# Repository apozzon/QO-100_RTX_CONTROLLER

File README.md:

# QO-100_RTX_CONTROLLER
QO-100 RTX CONTROLLER
ESP32 CONTROLLER for QO100
 	 	 	 	 	 	 	 	 	 	 	 	 	 	 	 	 
 	QO-100 RTX		IP		SSID		PASSW	 
 	Controller		192.168.0.214		SKYAP2		************	 
 																 
 	ON/OFF		DATV		GPSDO		FAN		…		…		…		…	 

 	V in		V pow		A pow		mW in		W out		W ref		SWR		T air-pow	 
 	13.8		27.5		1.5		10		7,5		0,6		1,788789		19-33	 

DRAFT COPY - SOON IN ENGLISH

Misure
Parametro	Max	PIN	Note
V ingresso	13.8 V	1	Partitore 1:10
V potenza	30V	2	Partitore 1:10
A potenza	10A	3	Parallelo a R 0,1 ohm da 5 W (10A = 1V)
W power in 	5V	4	
W power out	5V	5	
W reflected	5V	6	
C temperatura	60C	11	Apposito modulo digitale

Controlli
Parametro	Stato	PIN	Note
On / Off	0-1	7	Accende e spegne SDR – Arduino sempre on low
DATV	0-1	8	Commuta 12V-18V su Bias-T
Heat	0-1	9	Accende resistenza riscaldamento clima freddo

INSTALLAZIONE IDE E SETTAGGIO BOARD
Setup Steps for Arduino IDE
1.	Open Arduino IDE and go to File > Preferences.
2.	Add Board Manager URL: Paste the following into the "Additional Boards Manager URLs" field:
https://raw.githubusercontent.com/espressif/arduino-esp32/gh-pages/package_esp32_index.json.
3.	Install Boards: Go to Tools > Board > Boards Manager, search for "esp32" and install the latest version by Espressif Systems.
 
NB: se non carica support mettere queste due istruzioni in C:\Users\Andrea.DESKTOP-IK5K4JJ\.arduinoIDE\ arduino-cli.yaml
network:
  connection_timeout: 300s

4.	Select Board: Select Tools > Board > ESP32 Arduino > ESP32S3 Dev Module.
5.	Configure Tools Menu (Crucial for N16R8):
1.	USB CDC On Boot: "Enabled" (Allows Serial.print via USB).
2.	Flash Size: "16MB (128Mb)".
3.	Flash Mode: "QIO 80MHz" or "QOIO 80MHz".
4.	Partition Scheme: "16M Flash (3M APP/9.9M FATFS)" or similar large partition.
5.	PSRAM: "OPI PSRAM".
6.	Upload: Connect the board, select the correct Port, and upload a test sketch. 

ARDUINO
Additional board manager URL: https://espressif.github.io/arduino-esp32/package_esp32_index.json
Board scelta : ESP32S3 Dev Module

Librerie
https://github.com/ESP32Async/AsyncTCP
https://github.com/ESP32Async/ESPAsyncWebServer
DHT kxn

Java aggiunta libreria Google json
tasto destro su Progetto – Build Path -Add External Archives) – Scegliere file scaricato (es.  gson-2.3.1.jar)

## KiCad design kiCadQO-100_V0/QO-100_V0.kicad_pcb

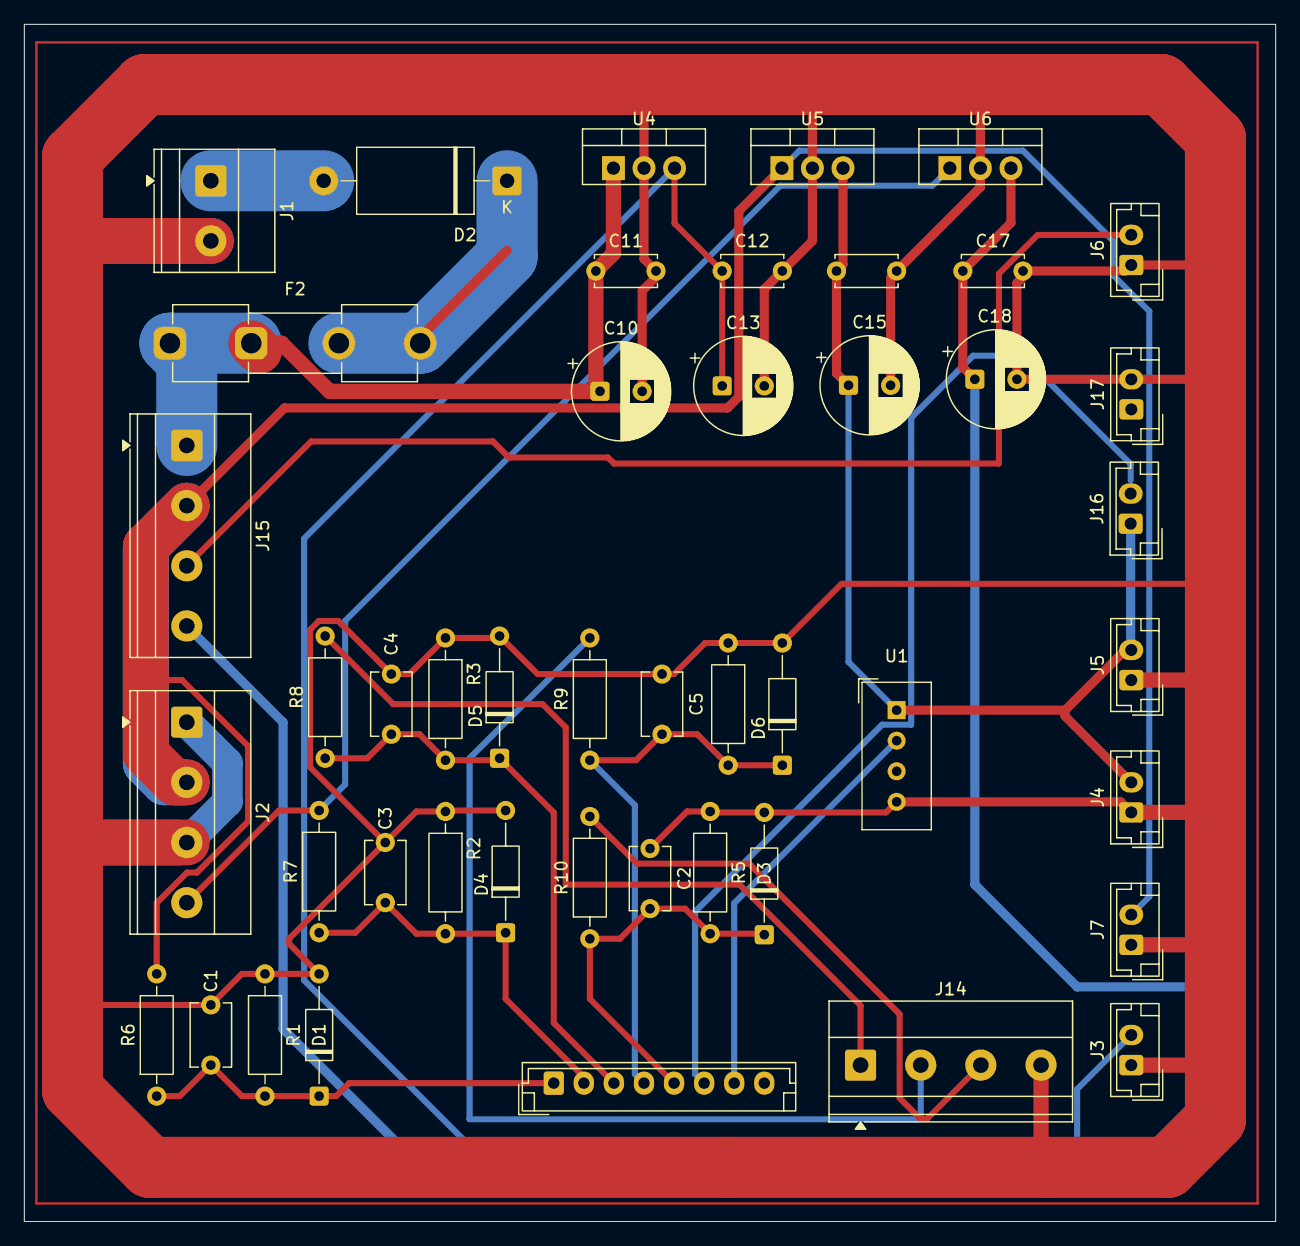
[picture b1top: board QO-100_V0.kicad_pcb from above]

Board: 2 copper layers, 104.0 x 99.5 mm, 46 parts (0 on the bottom side), 20 nets.

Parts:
C1, C2, C3, C4, C5: 100n; C_Disc_D5.1mm_W3.2mm_P5.00mm
C10, C13, C15, C18: 100uF; CP_Radial_D8.0mm_P3.50mm
C11: 330uF; C_Disc_D5.0mm_W2.5mm_P5.00mm
C12, C14, C17: 100nF; C_Disc_D5.0mm_W2.5mm_P5.00mm
D1, D3, D4, D5, D6: 3.3V; D_DO-35_SOD27_P10.16mm_Horizontal
D2: D_Zener 50V-20A; D_DO-27_P15.24mm_Horizontal
F2: Fuse; Fuseholder_Clip-5x20mm_Eaton_1A5601-01_Inline_P20.80x6.76mm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
J1: Conn_01x02; TerminalBlock_Phoenix_MKDS-1,5-2_1x02_P5.00mm_Horizontal
J2: TO DC/DC; TerminalBlock_Phoenix_MKDS-1,5-4_1x04_P5.00mm_Horizontal
J3: ESP32; JST_EH_B2B-EH-A_1x02_P2.50mm_Vertical
J4: Pluto; JST_EH_B2B-EH-A_1x02_P2.50mm_Vertical
J5: GPSDO; JST_EH_B2B-EH-A_1x02_P2.50mm_Vertical
J6: Bias-T; JST_EH_B2B-EH-A_1x02_P2.50mm_Vertical
J7: Preamp; JST_EH_B2B-EH-A_1x02_P2.50mm_Vertical
J13: TO ESP32 Measures; JST_EH_B8B-EH-A_1x08_P2.50mm_Vertical
J14: TO PA - measures; TerminalBlock_Phoenix_MKDS-1,5-4_1x04_P5.00mm_Horizontal
J15: TO RELAIS; TerminalBlock_Phoenix_MKDS-1,5-4_1x04_P5.00mm_Horizontal
J16: TO DHT PA temp; JST_EH_B2B-EH-A_1x02_P2.50mm_Vertical
J17: 5V data n GND; JST_EH_B2B-EH-A_1x02_P2.50mm_Vertical
R1, R3, R4, R5: 20k; R_Axial_DIN0207_L6.3mm_D2.5mm_P10.16mm_Horizontal
R2: 10k; R_Axial_DIN0207_L6.3mm_D2.5mm_P10.16mm_Horizontal
R6, R7, R8, R9, R10: 120k; R_Axial_DIN0207_L6.3mm_D2.5mm_P10.16mm_Horizontal
U1: DHT22 air; Aosong_DHT11_5.5x12.0_P2.54mm
U4, U5: L7805; TO-220-3_Vertical
U6: L7818; TO-220-3_Vertical

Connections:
/IO10: J13.7, U1.2 (DATA)
/IO11: J13.6, J16.2
/Power Supply and partitors/5V Pluto: C14.1, C15.1, J4.2, J5.2, J16.1, U1.1 (VDD), U5.3 (OUT)
/Power Supply and partitors/5V R: C12.1, C13.1, J3.2, U4.3 (OUT)
/Power Supply and partitors/12V: J2.2, J7.2, J15.2, R6.2, U5.1 (IN)
/Power Supply and partitors/12V in R: C10.1, C11.1, F2.1, J15.1, U4.1 (IN)
/Power Supply and partitors/18V R: C17.1, C18.1, J15.4, U6.3 (OUT)
/Power Supply and partitors/28V: J2.4, R7.2, U6.1 (IN)
/Power Supply and partitors/BIAS-T: J6.2, J15.3
GND: C1.1, C2.1, C3.1, C4.1, C5.1, C10.2, C11.2, C12.2, C13.2, C14.2, C15.2, C17.2, C18.2, D1.2 (A), D3.2 (A), D4.2 (A), D5.2 (A), D6.2 (A), J1.2, J2.1, J2.3, J3.1, J4.1, J5.1, J6.1, J7.1, J14.4, J17.2, R1.1, R2.1, R3.1, R4.1, R5.1, U1.4 (GND), U4.2 (GND), U5.2 (GND), U6.2 (GND)
unnamed: C1.2, D1.1 (K), J13.1, R1.2, R6.1
unnamed: D2.2 (A), J1.1
unnamed: D2.1 (K), F2.2
unnamed: C2.2, D3.1 (K), J13.5, R5.2, R10.1
unnamed: C3.2, D4.1 (K), J13.2, R2.2, R7.1
unnamed: C4.2, D5.1 (K), J13.3, R3.2, R8.1
unnamed: C5.2, D6.1 (K), J13.4, R4.2, R9.1
PA W in: J14.1, R8.2
PA W out: J14.2, R9.2
PA W ref: J14.3, R10.2

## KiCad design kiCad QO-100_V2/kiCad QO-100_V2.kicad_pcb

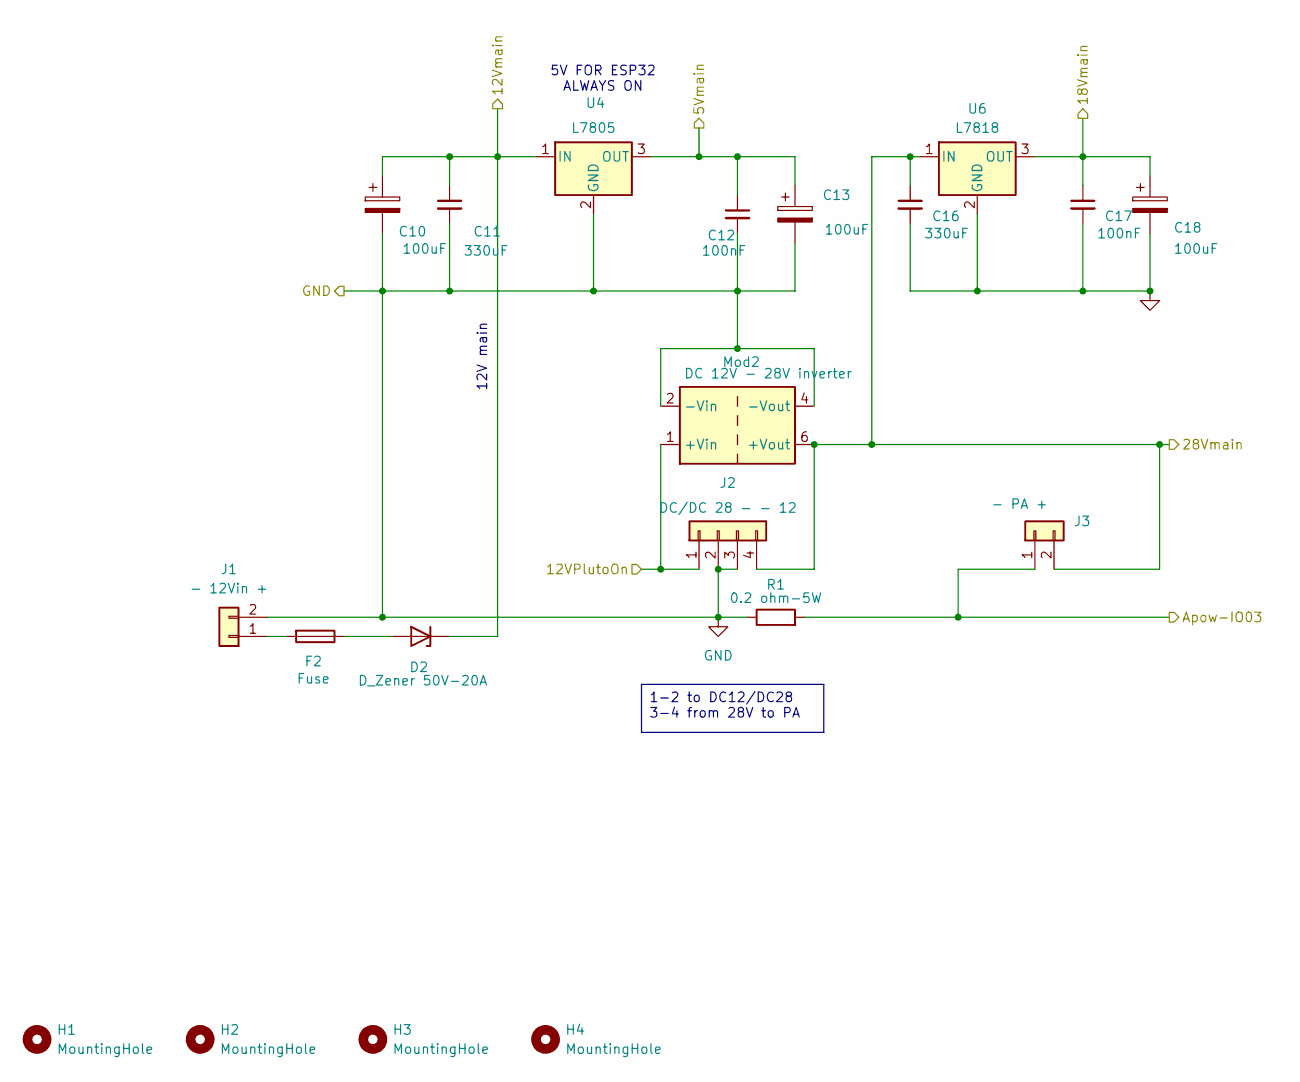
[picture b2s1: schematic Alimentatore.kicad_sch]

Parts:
C10, C13, C18: 100uF; CP_Radial_D8.0mm_P3.50mm
C11, C16: 330uF; C_Disc_D5.0mm_W2.5mm_P5.00mm
C12, C17: 100nF; C_Disc_D5.0mm_W2.5mm_P5.00mm
D2: D_Zener 50V-20A; D_DO-27_P15.24mm_Horizontal
F2: Fuse; Fuseholder_Clip-5x20mm_Eaton_1A5601-01_Inline_P20.80x6.76mm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
H1, H2, H3, H4: MountingHole; MountingHole_3.2mm_M3
J1: - 12Vin +; TerminalBlock_Phoenix_MKDS-1,5-2_1x02_P5.00mm_Horizontal
J2: DC/DC 28 - - 12; TerminalBlock_Phoenix_MKDS-1,5-4_1x04_P5.00mm_Horizontal
J3: - PA +; TerminalBlock_Phoenix_MKDS-1,5-2_1x02_P5.00mm_Horizontal
Mod2: DC 12V - 28V inverter; Converter_DCDC_TRACO_TRA3-xxxx_THT
R1: 0.2 ohm-5W; R_Axial_Power_L20.0mm_W6.4mm_P25.40mm
U4: L7805; TO-220-3_Vertical
U6: L7818; TO-220-3_Vertical

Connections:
/ESP32-S3-DevBoard/5Vmain: C12.1, C13.1, U4.3 (OUT); also elsewhere on the board
/ESP32-S3-DevBoard/12VPlutoOn: J2.1, Mod2.1 (+Vin); also elsewhere on the board
/ESP32-S3-DevBoard/12Vmain: C10.1, C11.1, D2.1 (K), U4.1 (IN); also elsewhere on the board
/ESP32-S3-DevBoard/18Vmain: C17.1, C18.1, U6.3 (OUT); also elsewhere on the board
/ESP32-S3-DevBoard/28Vmain: C16.1, J2.4, J3.2, Mod2.6 (+Vout), U6.1 (IN); also elsewhere on the board
/ESP32-S3-DevBoard/Apow-IO03: J3.1, R1.2; also elsewhere on the board
GND: C10.2, C11.2, C12.2, C13.2, C16.2, C17.2, C18.2, J1.2, J2.2, J2.3, Mod2.2 (-Vin), Mod2.4 (-Vout), R1.1, U4.2 (GND), U6.2 (GND); also elsewhere on the board
unnamed: D2.2 (A), F2.1
unnamed: F2.2, J1.1

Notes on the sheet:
5V FOR ESP32 ALWAYS ON
12V main
1-2 to DC12/DC28 3-4 from 28V to PA

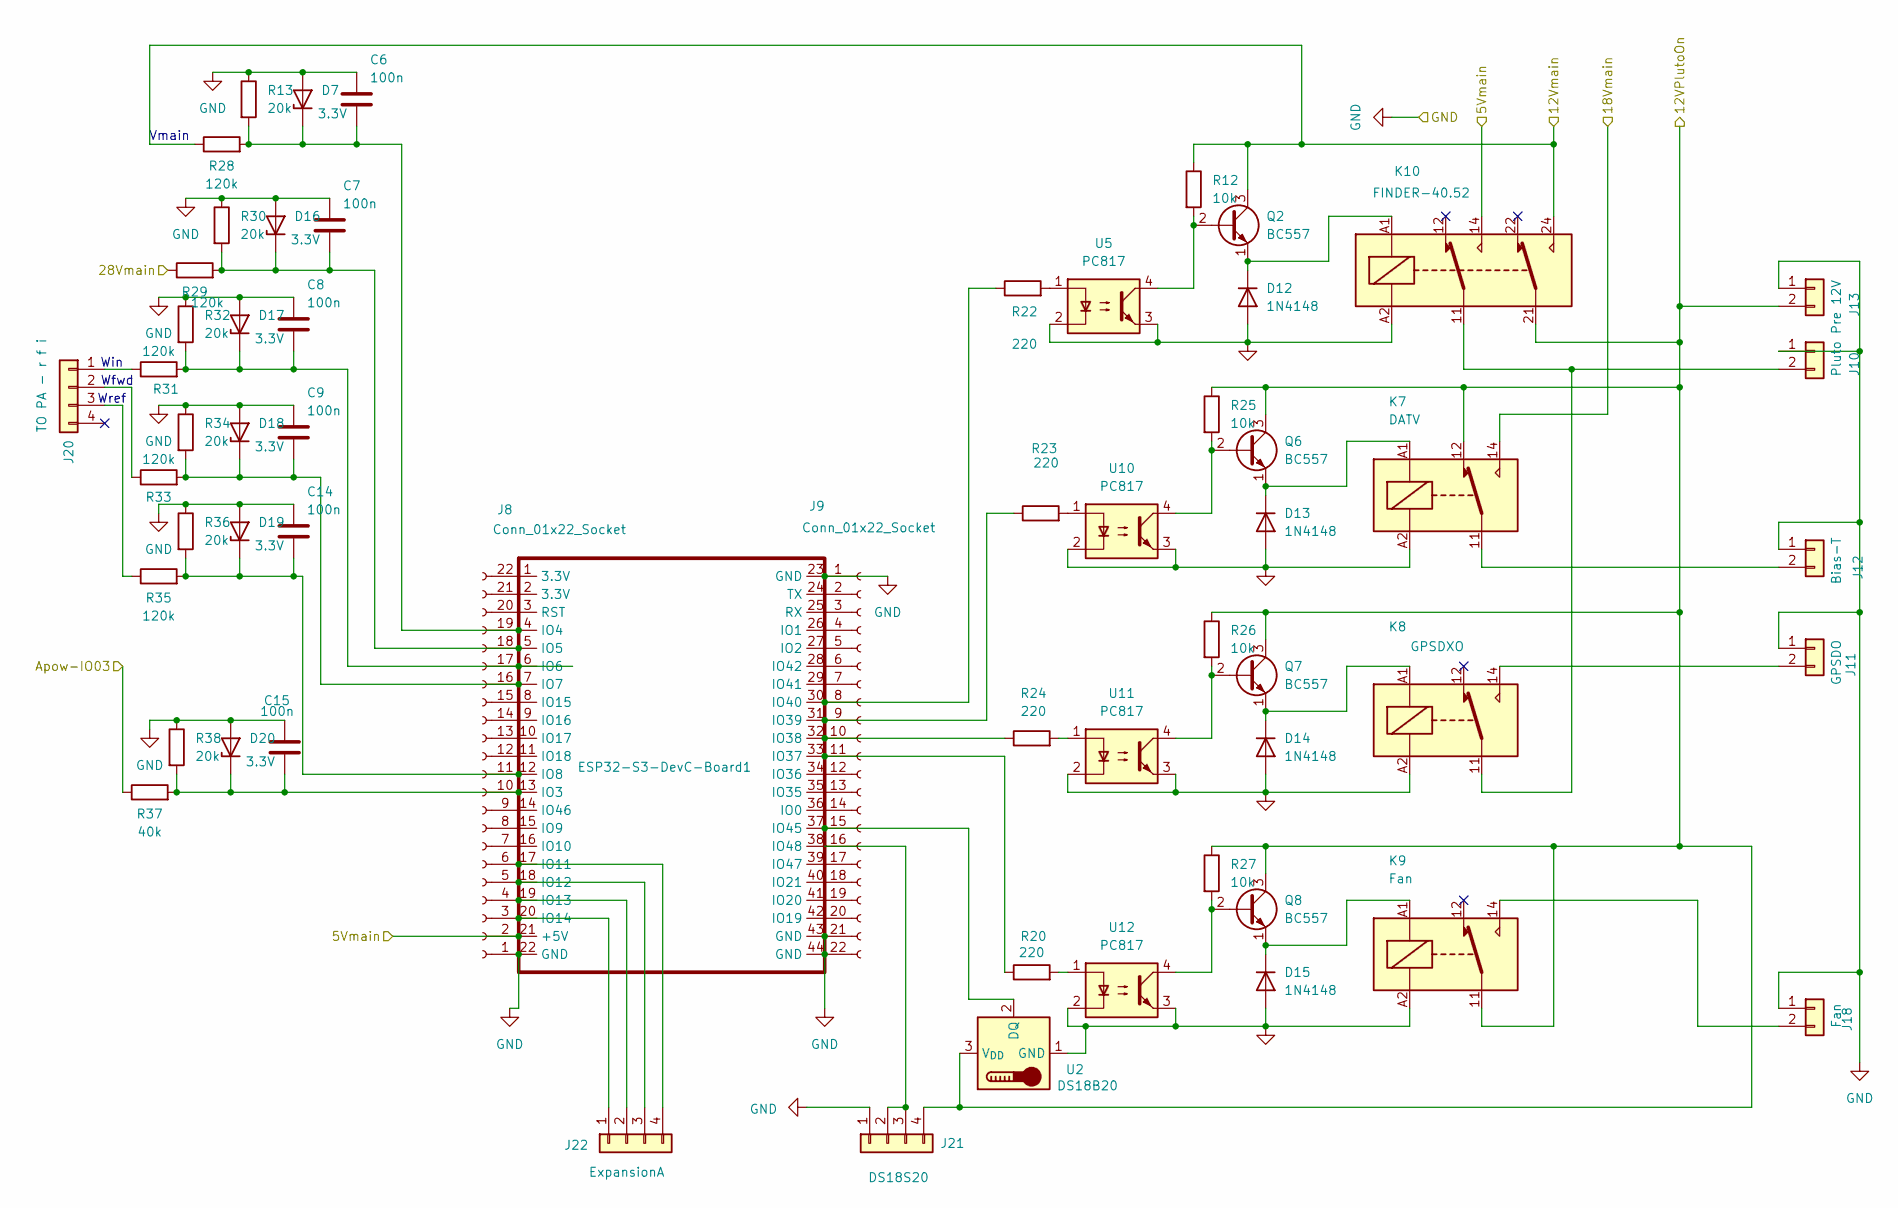
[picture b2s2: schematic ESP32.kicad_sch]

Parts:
C6, C7, C8, C9, C14, C15: 100n; C_Disc_D5.1mm_W3.2mm_P5.00mm
D7, D16, D17, D18, D19, D20: 3.3V; D_DO-35_SOD27_P10.16mm_Horizontal
D12, D13, D14, D15: 1N4148; D_DO-35_SOD27_P7.62mm_Horizontal
ESP32-S3-DevC-Board1: (no value)
J8, J9: Conn_01x22_Socket; PinSocket_1x22_P2.54mm_Vertical
J10: Pluto; JST_EH_B2B-EH-A_1x02_P2.50mm_Vertical
J11: GPSDO; JST_EH_B2B-EH-A_1x02_P2.50mm_Vertical
J12: Bias-T; JST_EH_B2B-EH-A_1x02_P2.50mm_Vertical
J13: Pre 12V; JST_EH_B2B-EH-A_1x02_P2.50mm_Vertical
J18: Fan; JST_EH_B2B-EH-A_1x02_P2.50mm_Vertical
J20: TO PA - r f i; TerminalBlock_Phoenix_MKDS-1,5-4_1x04_P5.00mm_Horizontal
J21: DS18S20; TerminalBlock_Phoenix_MKDS-1,5-4_1x04_P5.00mm_Horizontal
J22: ExpansionA; TerminalBlock_Phoenix_MKDS-1,5-4_1x04_P5.00mm_Horizontal
K7: DATV; Relay_SPDT_Finder_32.21-x000
K8: GPSDXO; Relay_SPDT_Finder_32.21-x000
K9: Fan; Relay_SPDT_Finder_32.21-x000
K10: FINDER-40.52; Relay_DPDT_Finder_40.52
Q2, Q6, Q7, Q8: BC557; TO-92_HandSolder
R12, R25, R26, R27: 10k; R_Axial_DIN0207_L6.3mm_D2.5mm_P10.16mm_Horizontal
R13, R30, R32, R34, R36, R38: 20k; R_Axial_DIN0207_L6.3mm_D2.5mm_P10.16mm_Horizontal
R20, R22, R23, R24: 220; R_Axial_DIN0207_L6.3mm_D2.5mm_P10.16mm_Horizontal
R28, R29, R31, R33, R35: 120k; R_Axial_DIN0207_L6.3mm_D2.5mm_P10.16mm_Horizontal
R37: 40k; R_Axial_DIN0207_L6.3mm_D2.5mm_P10.16mm_Horizontal
U2: DS18B20; TO-92_Inline
U5, U10, U11, U12: PC817; DIP-4_W7.62mm

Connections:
/ESP32-S3-DevBoard/5Vmain: ESP32-S3-DevC-Board1.21 (+5V), J8.2, K10.14; also elsewhere on the board
/ESP32-S3-DevBoard/12VPlutoOn: J13.2, J21.4, K7.12, K9.11, K10.21, Q6.3 (C), Q7.3 (C), Q8.3 (C), R25.1, R26.1, R27.1, U2.3 (V_{DD}); also elsewhere on the board
/ESP32-S3-DevBoard/12Vmain: K10.24, Q2.3 (C), R12.1, R28.1; also elsewhere on the board
/ESP32-S3-DevBoard/18Vmain: K7.14; also elsewhere on the board
/ESP32-S3-DevBoard/28Vmain: R29.1; also elsewhere on the board
/ESP32-S3-DevBoard/Apow-IO03: R37.1; also elsewhere on the board
GND: C6.1, C7.1, C8.1, C9.1, C14.1, C15.1, D7.2 (A), D12.2 (A), D13.2 (A), D14.2 (A), D15.2 (A), D16.2 (A), D17.2 (A), D18.2 (A), D19.2 (A), D20.2 (A), ESP32-S3-DevC-Board1.22 (GND), ESP32-S3-DevC-Board1.23 (GND), ESP32-S3-DevC-Board1.43 (GND), ESP32-S3-DevC-Board1.44 (GND), J8.1, J9.1, J9.21, J9.22, J10.1, J11.1, J12.1, J13.1, J18.1, J21.1, K7.A2, K8.A2, K9.A2, K10.A2, R13.1, R30.1, R32.1, R34.1, R36.1, R38.1, U2.1 (GND), U5.2, U5.3, U10.2, U10.3, U11.2, U11.3, U12.2, U12.3; also elsewhere on the board
unnamed: C6.2, D7.1 (K), ESP32-S3-DevC-Board1.4 (IO4), J8.19, R13.2, R28.2
unnamed: D12.1 (K), K10.A1, Q2.1 (E)
unnamed: D13.1 (K), K7.A1, Q6.1 (E)
unnamed: D14.1 (K), K8.A1, Q7.1 (E)
unnamed: D15.1 (K), K9.A1, Q8.1 (E)
unnamed: C7.2, D16.1 (K), ESP32-S3-DevC-Board1.5 (IO5), J8.18, R29.2, R30.2
unnamed: C8.2, D17.1 (K), ESP32-S3-DevC-Board1.6 (IO6), J8.17, R31.2, R32.2
unnamed: C9.2, D18.1 (K), ESP32-S3-DevC-Board1.7 (IO7), J8.16, R33.2, R34.2
unnamed: C14.2, D19.1 (K), ESP32-S3-DevC-Board1.12 (IO8), J8.11, R35.2, R36.2
unnamed: C15.2, D20.1 (K), ESP32-S3-DevC-Board1.13 (IO3), J8.10, R37.2, R38.2
unnamed: ESP32-S3-DevC-Board1.36 (IO0), J9.14
unnamed: ESP32-S3-DevC-Board1.26 (IO1), J9.4
unnamed: ESP32-S3-DevC-Board1.27 (IO2), J9.5
unnamed: ESP32-S3-DevC-Board1.15 (IO9), J8.8
unnamed: ESP32-S3-DevC-Board1.16 (IO10), J8.7
unnamed: ESP32-S3-DevC-Board1.17 (IO11), J8.6, J22.4
unnamed: ESP32-S3-DevC-Board1.18 (IO12), J8.5, J22.3
unnamed: ESP32-S3-DevC-Board1.19 (IO13), J8.4, J22.2
unnamed: ESP32-S3-DevC-Board1.20 (IO14), J8.3, J22.1
unnamed: ESP32-S3-DevC-Board1.8 (IO15), J8.15
unnamed: ESP32-S3-DevC-Board1.9 (IO16), J8.14
unnamed: ESP32-S3-DevC-Board1.10 (IO17), J8.13
unnamed: ESP32-S3-DevC-Board1.11 (IO18), J8.12
unnamed: ESP32-S3-DevC-Board1.42 (IO19), J9.20
unnamed: ESP32-S3-DevC-Board1.41 (IO20), J9.19
unnamed: ESP32-S3-DevC-Board1.40 (IO21), J9.18
unnamed: ESP32-S3-DevC-Board1.35 (IO35), J9.13
unnamed: ESP32-S3-DevC-Board1.34 (IO36), J9.12
unnamed: ESP32-S3-DevC-Board1.33 (IO37), J9.11, R20.1
unnamed: ESP32-S3-DevC-Board1.32 (IO38), J9.10, R24.1
unnamed: ESP32-S3-DevC-Board1.31 (IO39), J9.9, R23.1
unnamed: ESP32-S3-DevC-Board1.30 (IO40), J9.8, R22.1
unnamed: ESP32-S3-DevC-Board1.29 (IO41), J9.7
unnamed: ESP32-S3-DevC-Board1.28 (IO42), J9.6
unnamed: ESP32-S3-DevC-Board1.37 (IO45), J9.15, U2.2 (DQ)
unnamed: ESP32-S3-DevC-Board1.14 (IO46), J8.9
unnamed: ESP32-S3-DevC-Board1.39 (IO47), J9.17
unnamed: ESP32-S3-DevC-Board1.38 (IO48), J9.16, J21.2, J21.3
unnamed: ESP32-S3-DevC-Board1.3 (RST), J8.20
unnamed: ESP32-S3-DevC-Board1.25 (RX), J9.3
unnamed: ESP32-S3-DevC-Board1.24 (TX), J9.2
unnamed: ESP32-S3-DevC-Board1.2 (3.3V), J8.21
unnamed: ESP32-S3-DevC-Board1.1 (3.3V), J8.22
unnamed: J10.2, K8.11, K10.11
unnamed: J11.2, K8.14
unnamed: J12.2, K7.11
unnamed: J18.2, K9.14
unnamed: J20.1, R31.1
unnamed: J20.2, R33.1
unnamed: J20.3, R35.1
unnamed: Q2.2 (B), R12.2, U5.4
unnamed: Q6.2 (B), R25.2, U10.4
unnamed: Q7.2 (B), R26.2, U11.4
unnamed: Q8.2 (B), R27.2, U12.4
unnamed: R20.2, U12.1
unnamed: R22.2, U5.1
unnamed: R23.2, U10.1
unnamed: R24.2, U11.1

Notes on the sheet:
Wref
Vmain
Win
Wfwd

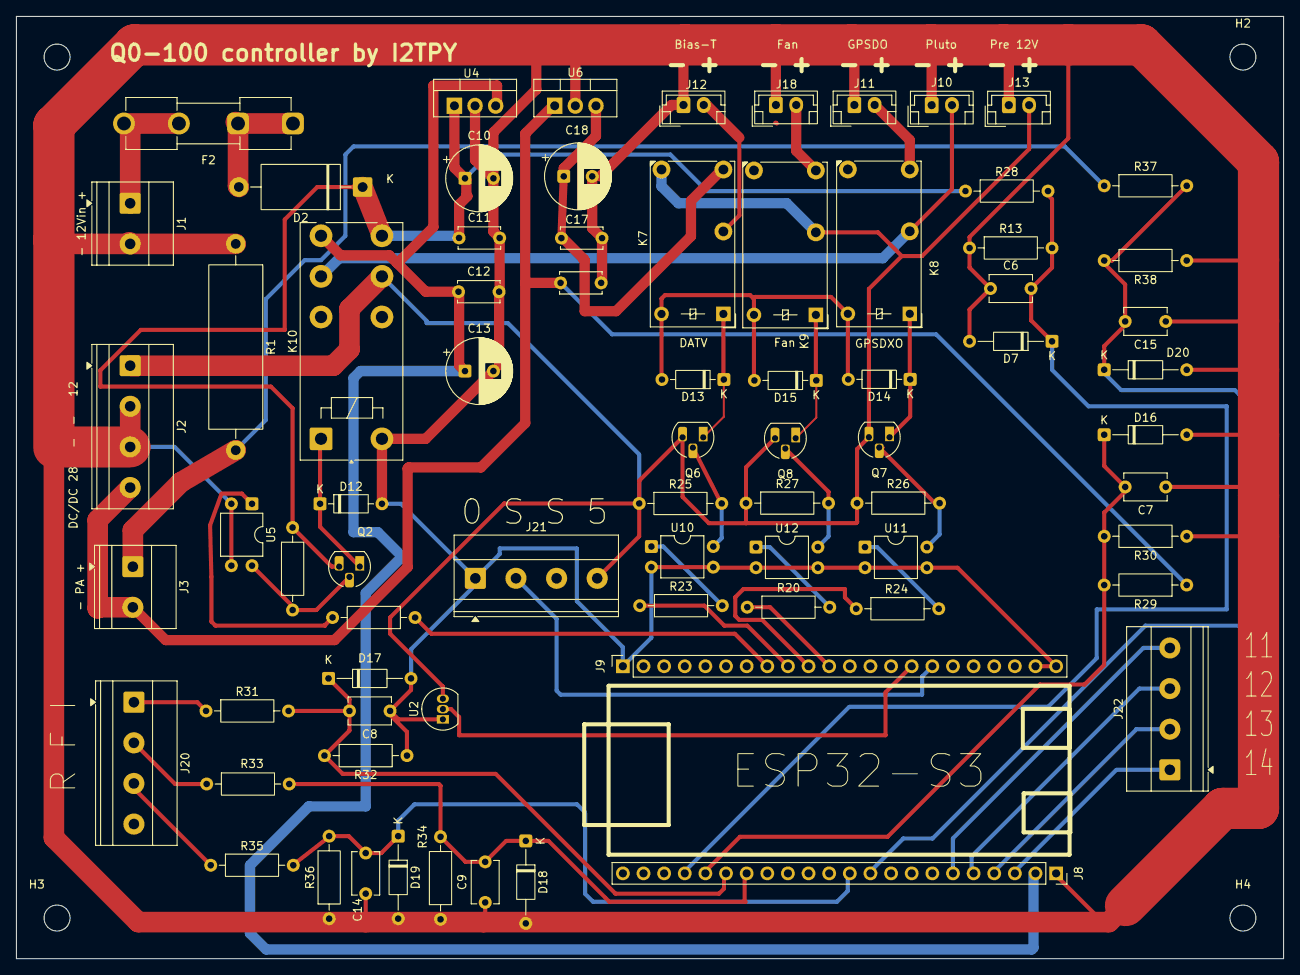
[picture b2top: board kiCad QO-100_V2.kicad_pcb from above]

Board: 2 copper layers, 156.0 x 116.0 mm, 78 parts (0 on the bottom side), 44 nets.

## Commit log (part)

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2026-02-14 Create src
2026-02-14 Create s
2026-02-14 Create a
2026-03-09 Create ESP32
